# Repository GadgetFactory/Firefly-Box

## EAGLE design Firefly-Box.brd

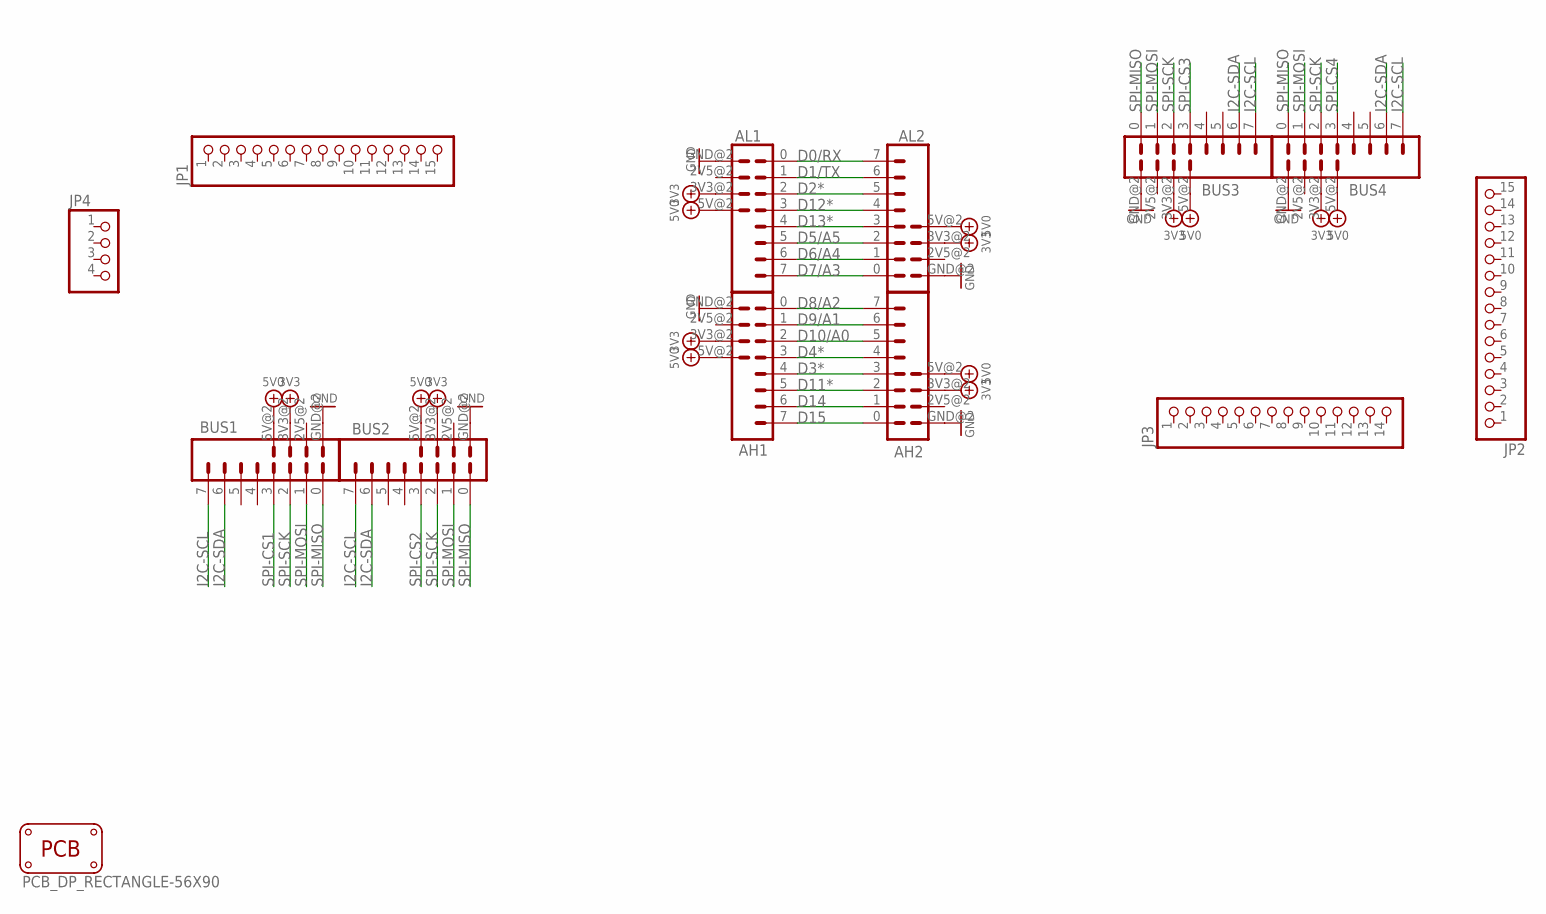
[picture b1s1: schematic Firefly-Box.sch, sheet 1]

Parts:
AH1, AH2: WING8WING8_NOHOLES; WINGSIDE_8BIT_NOHOLES
AL1, AL2: WING8WING8_NOHOLES; WINGSIDE_8BIT_NOHOLES
BUS1, BUS2, BUS3, BUS4: WING8WING8_NOHOLES; WINGSIDE_8BIT_NOHOLES
JP1, JP2: PINHD-1X15; 1X15
JP3: PINHD-1X14; 1X14
JP4: PINHD-1X4; 1X04
PCB2: PCB_DP_RECTANGLE-56X90; DP9056_V1

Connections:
3V3: AH1.3V3@2 (3V3), AH2.3V3@2 (3V3), AL1.3V3@2 (3V3), AL2.3V3@2 (3V3), BUS1.3V3@2 (3V3), BUS2.3V3@2 (3V3), BUS3.3V3@2 (3V3), BUS4.3V3@2 (3V3); also elsewhere on the board
5V0: AH1.5V@2 (5V), AH2.5V@2 (5V), AL1.5V@2 (5V), AL2.5V@2 (5V), BUS1.5V@2 (5V), BUS2.5V@2 (5V), BUS3.5V@2 (5V), BUS4.5V@2 (5V); also elsewhere on the board
D0/RX: AL1.0 (1), AL2.7 (8); also elsewhere on the board
D1/TX: AL1.1 (2), AL2.6 (7); also elsewhere on the board
D2*: AL1.2 (3), AL2.5 (6); also elsewhere on the board
D3*: AH1.4 (5), AH2.3 (4); also elsewhere on the board
D4*: AH1.3 (4), AH2.4 (5); also elsewhere on the board
D5/A5: AL1.5 (6), AL2.2 (3); also elsewhere on the board
D6/A4: AL1.6 (7), AL2.1 (2); also elsewhere on the board
D7/A3: AL1.7 (8), AL2.0 (1); also elsewhere on the board
D8/A2: AH1.0 (1), AH2.7 (8); also elsewhere on the board
D9/A1: AH1.1 (2), AH2.6 (7); also elsewhere on the board
D10/A0: AH1.2 (3), AH2.5 (6); also elsewhere on the board
D11*: AH1.5 (6), AH2.2 (3); also elsewhere on the board
D12*: AL1.3 (4), AL2.4 (5); also elsewhere on the board
D13*: AL1.4 (5), AL2.3 (4); also elsewhere on the board
D14: AH1.6 (7), AH2.1 (2); also elsewhere on the board
D15: AH1.7 (8), AH2.0 (1); also elsewhere on the board
GND: AH1.GND@2 (GND), AH2.GND@2 (GND), AL1.GND@2 (GND), AL2.GND@2 (GND), BUS1.GND@2 (GND), BUS2.GND@2 (GND), BUS3.GND@2 (GND), BUS4.GND@2 (GND); also elsewhere on the board
I2C-SCL: BUS1.7 (8), BUS2.7 (8), BUS3.7 (8), BUS4.7 (8); also elsewhere on the board
I2C-SDA: BUS1.6 (7), BUS2.6 (7), BUS3.6 (7), BUS4.6 (7); also elsewhere on the board
SPI-CS1: BUS1.3 (4); also elsewhere on the board
SPI-CS2: BUS2.3 (4); also elsewhere on the board
SPI-CS3: BUS3.3 (4); also elsewhere on the board
SPI-CS4: BUS4.3 (4); also elsewhere on the board
SPI-MISO: BUS1.0 (1), BUS2.0 (1), BUS3.0 (1), BUS4.0 (1); also elsewhere on the board
SPI-MOSI: BUS1.1 (2), BUS2.1 (2), BUS3.1 (2), BUS4.1 (2); also elsewhere on the board
SPI-SCK: BUS1.2 (3), BUS2.2 (3), BUS3.2 (3), BUS4.2 (3); also elsewhere on the board

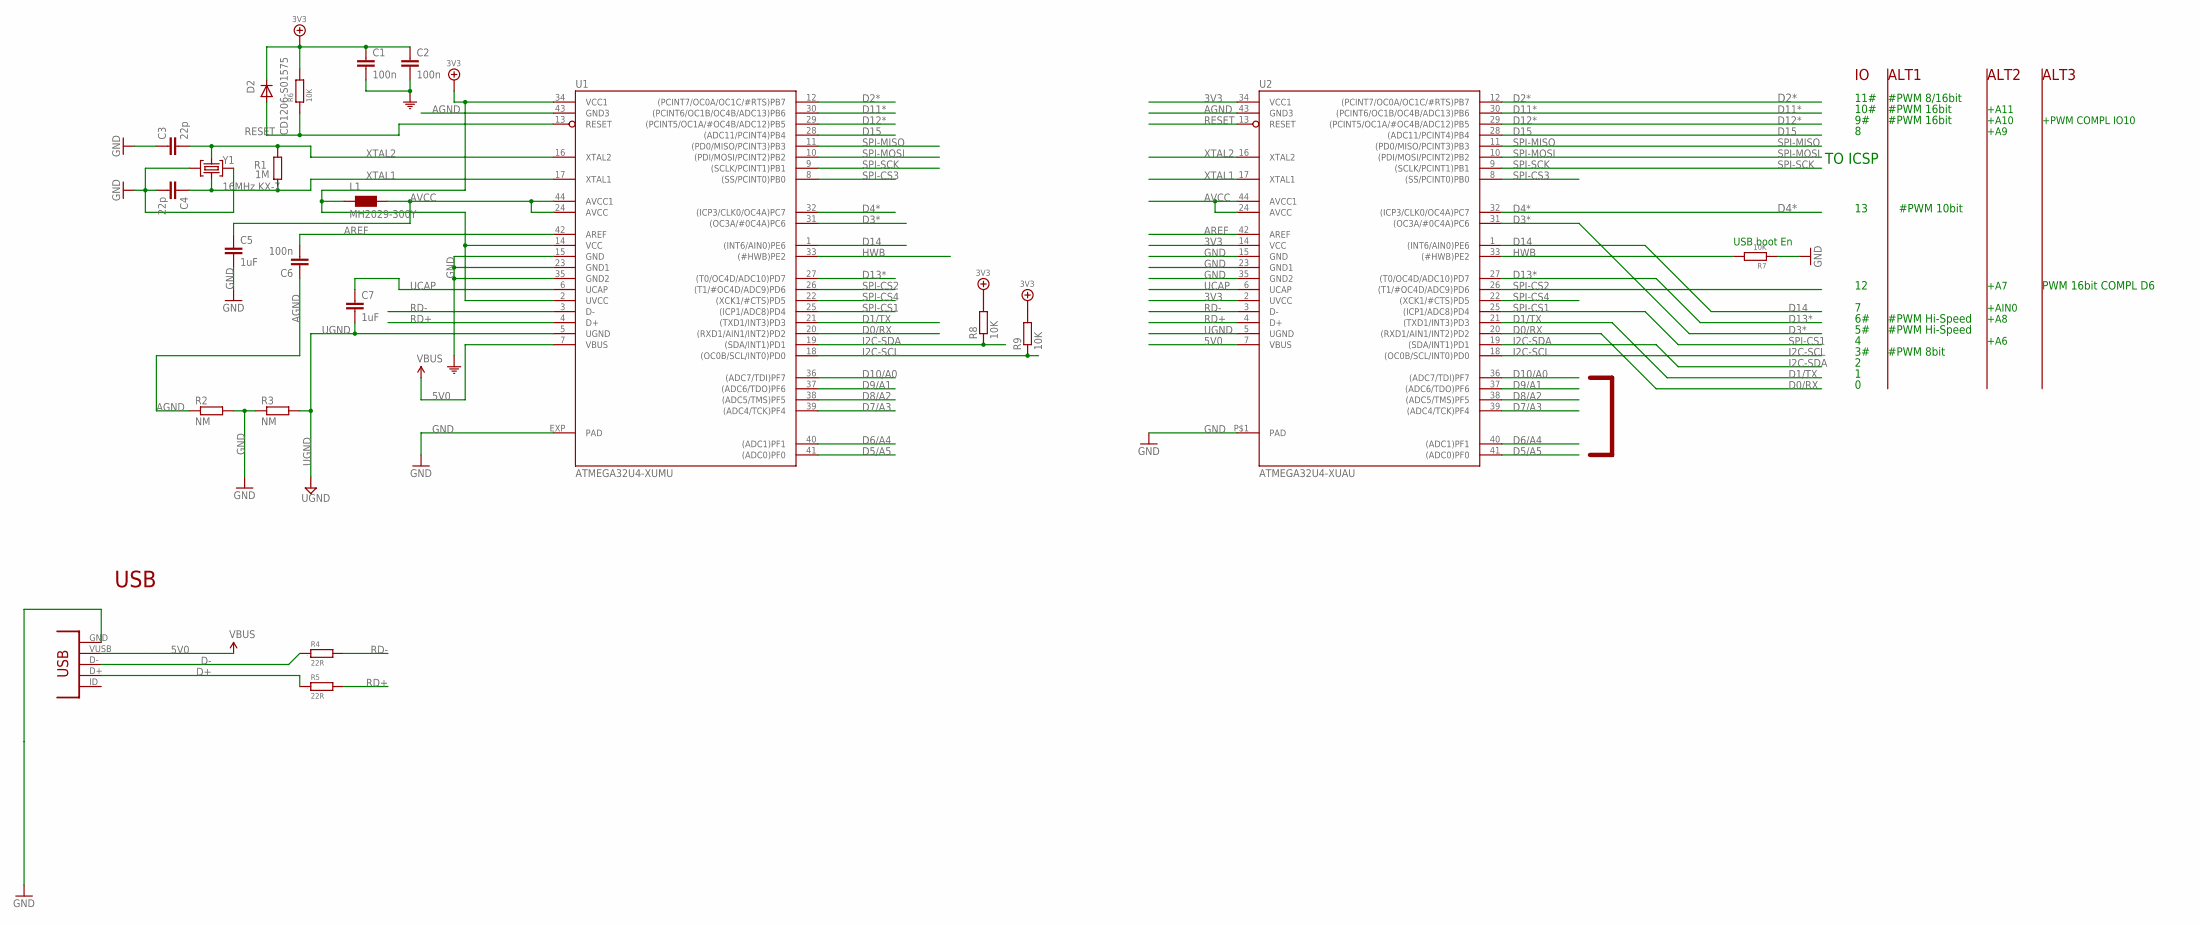
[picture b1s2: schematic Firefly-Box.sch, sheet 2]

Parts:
C1, C2, C6: 100n; C0603-ROUND
C3, C4: 22p; C0603-ROUND
C5, C7: 1uF; C0603-ROUND
CONN2: CONN_USB; CONN_USB_MINI-B
D2: CD1206-S01575; MINIMELF
L1: MH2029-300Y; 0805
R1: 1M; R0603-ROUND
R2, R3: NM; R0402
R4, R5: 22R; 0805
R6, R7: 10K; 0805
R8, R9: 10K; R0402
U1: ATMEGA32U4-XUMU; QFN44ML7X7
U2: ATMEGA32U4-XUAU; TQFP44-PAD
Y1: 16MHz KX-7; CRYSTAL-3.2-2.5

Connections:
3V3: C1.1, C2.1, D2.C, L1.1, R6.2, R8.2, R9.2, U1.2 (UVCC), U1.14 (VCC), U1.34 (VCC1), U2.2 (UVCC), U2.14 (VCC), U2.34 (VCC1); also elsewhere on the board
5V0: CONN2.VUSB, U1.7 (VBUS), U2.7 (VBUS); also elsewhere on the board
AGND: C6.1, R2.1, U1.43 (GND3), U2.43 (GND3)
AREF: C6.2, U1.42 (AREF), U2.42 (AREF)
AVCC: C5.1, L1.2, U1.24 (AVCC), U1.44 (AVCC1), U2.24 (AVCC), U2.44 (AVCC1)
D0/RX: U1.20 ((RXD1/AIN1/INT2)PD2), U2.20 ((RXD1/AIN1/INT2)PD2); also elsewhere on the board
D1/TX: U1.21 ((TXD1/INT3)PD3), U2.21 ((TXD1/INT3)PD3); also elsewhere on the board
D2*: U1.12 ((PCINT7/OC0A/OC1C/#RTS)PB7), U2.12 ((PCINT7/OC0A/OC1C/#RTS)PB7); also elsewhere on the board
D3*: U1.31 ((OC3A/#0C4A)PC6), U2.31 ((OC3A/#0C4A)PC6); also elsewhere on the board
D4*: U1.32 ((ICP3/CLK0/OC4A)PC7), U2.32 ((ICP3/CLK0/OC4A)PC7); also elsewhere on the board
D5/A5: U1.41 ((ADC0)PF0), U2.41 ((ADC0)PF0); also elsewhere on the board
D6/A4: U1.40 ((ADC1)PF1), U2.40 ((ADC1)PF1); also elsewhere on the board
D7/A3: U1.39 ((ADC4/TCK)PF4), U2.39 ((ADC4/TCK)PF4); also elsewhere on the board
D8/A2: U1.38 ((ADC5/TMS)PF5), U2.38 ((ADC5/TMS)PF5); also elsewhere on the board
D9/A1: U1.37 ((ADC6/TDO)PF6), U2.37 ((ADC6/TDO)PF6); also elsewhere on the board
D10/A0: U1.36 ((ADC7/TDI)PF7), U2.36 ((ADC7/TDI)PF7); also elsewhere on the board
D11*: U1.30 ((PCINT6/OC1B/OC4B/ADC13)PB6), U2.30 ((PCINT6/OC1B/OC4B/ADC13)PB6); also elsewhere on the board
D12*: U1.29 ((PCINT5/OC1A/#OC4B/ADC12)PB5), U2.29 ((PCINT5/OC1A/#OC4B/ADC12)PB5); also elsewhere on the board
D13*: U1.27 ((T0/OC4D/ADC10)PD7), U2.27 ((T0/OC4D/ADC10)PD7); also elsewhere on the board
D14: U1.1 ((INT6/AIN0)PE6), U2.1 ((INT6/AIN0)PE6); also elsewhere on the board
D15: U1.28 ((ADC11/PCINT4)PB4), U2.28 ((ADC11/PCINT4)PB4); also elsewhere on the board
D+: CONN2.D+, R5.1
D-: CONN2.D-, R4.1
GND: C1.2, C2.2, C3.1, C4.2, C5.2, CONN2.GND, R2.2, R3.1, R7.1, U1.15 (GND), U1.23 (GND1), U1.35 (GND2), U1.EXP (PAD), U2.15 (GND), U2.23 (GND1), U2.35 (GND2), U2.P$1 (PAD), Y1.2 (GND), Y1.4 (GND); also elsewhere on the board
HWB: R7.2, U1.33 ((#HWB)PE2), U2.33 ((#HWB)PE2)
I2C-SCL: R9.1, U1.18 ((OC0B/SCL/INT0)PD0), U2.18 ((OC0B/SCL/INT0)PD0); also elsewhere on the board
I2C-SDA: R8.1, U1.19 ((SDA/INT1)PD1), U2.19 ((SDA/INT1)PD1); also elsewhere on the board
RD+: R5.2, U1.4 (D+), U2.4 (D+)
RD-: R4.2, U1.3 (D-), U2.3 (D-)
RESET: D2.A, R6.1, U1.13 (RESET), U2.13 (RESET)
SPI-CS1: U1.25 ((ICP1/ADC8)PD4), U2.25 ((ICP1/ADC8)PD4); also elsewhere on the board
SPI-CS2: U1.26 ((T1/#OC4D/ADC9)PD6), U2.26 ((T1/#OC4D/ADC9)PD6); also elsewhere on the board
SPI-CS3: U1.8 ((SS/PCINT0)PB0), U2.8 ((SS/PCINT0)PB0); also elsewhere on the board
SPI-CS4: U1.22 ((XCK1/#CTS)PD5), U2.22 ((XCK1/#CTS)PD5); also elsewhere on the board
SPI-MISO: U1.11 ((PD0/MISO/PCINT3)PB3), U2.11 ((PD0/MISO/PCINT3)PB3); also elsewhere on the board
SPI-MOSI: U1.10 ((PDI/MOSI/PCINT2)PB2), U2.10 ((PDI/MOSI/PCINT2)PB2); also elsewhere on the board
SPI-SCK: U1.9 ((SCLK/PCINT1)PB1), U2.9 ((SCLK/PCINT1)PB1); also elsewhere on the board
UCAP: C7.1, U1.6 (UCAP), U2.6 (UCAP)
UGND: C7.2, R3.2, U1.5 (UGND), U2.5 (UGND)
XTAL1: C4.1, R1.1, U1.17 (XTAL1), U2.17 (XTAL1), Y1.1 (C1)
XTAL2: C3.2, R1.2, U1.16 (XTAL2), U2.16 (XTAL2), Y1.3 (C2)

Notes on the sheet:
USB boot En
USB
TO ICSP
10#
11#
#PWM 8bit
#PWM Hi-Speed
#PWM 8/16bit
#PWM 16bit
PWM 16bit COMPL D6
#PWM 10bit
+A6
+A7
+A11
+A10
+A8
+A9
+PWM COMPL IO10
+AIN0
ALT1
ALT2
ALT3

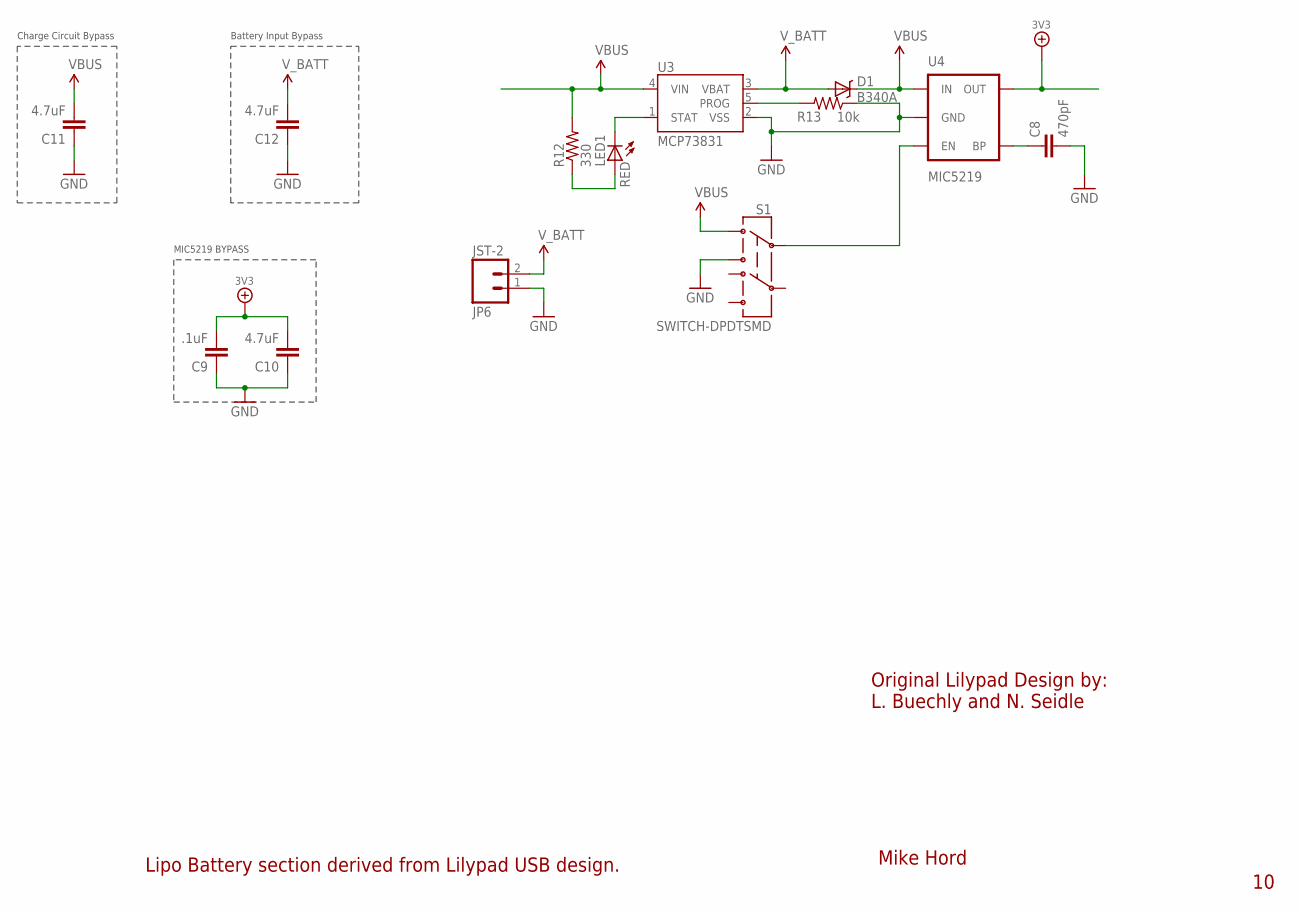
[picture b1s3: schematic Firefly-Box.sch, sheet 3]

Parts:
C8: 470pF; 0603-CAP
C9: .1uF; 0603-CAP
C10: 4.7uF; 0603-CAP
C11, C12: 4.7uF; 1206
D1: B340A; SMA-DIODE
JP6: JST-2; JST-2-SMD
LED1: RED; LED-0603
R12: 330; 0603-RES
R13: 10k; 0603-RES
S1: SWITCH-DPDTSMD; AYZ0202
U3: MCP73831; SOT23-5
U4: MIC5219; SOT23-5

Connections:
3V3: C9.2, C10.2, U4.5 (OUT); also elsewhere on the board
5V0: C11.2, D1.C, R12.2, S1.1, U3.4 (VIN), U4.1 (IN); also elsewhere on the board
GND: C8.2, C9.1, C10.1, C11.1, C12.1, JP6.1 (2), R13.1, S1.3, U3.2 (VSS), U4.2 (GND); also elsewhere on the board
unnamed: S1.2, U4.3 (EN)
unnamed: LED1.A, R12.1
unnamed: LED1.C, U3.1 (STAT)
unnamed: R13.2, U3.5 (PROG)
unnamed: C8.1, U4.4 (BP)
V_BATT: C12.2, D1.A, JP6.2 (1), U3.3 (VBAT)

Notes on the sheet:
MIC5219 BYPASS
Mike Hord
Original Lilypad Design by:
L. Buechly and N. Seidle
Charge Circuit Bypass
Battery Input Bypass
Lipo Battery section derived from Lilypad USB design.

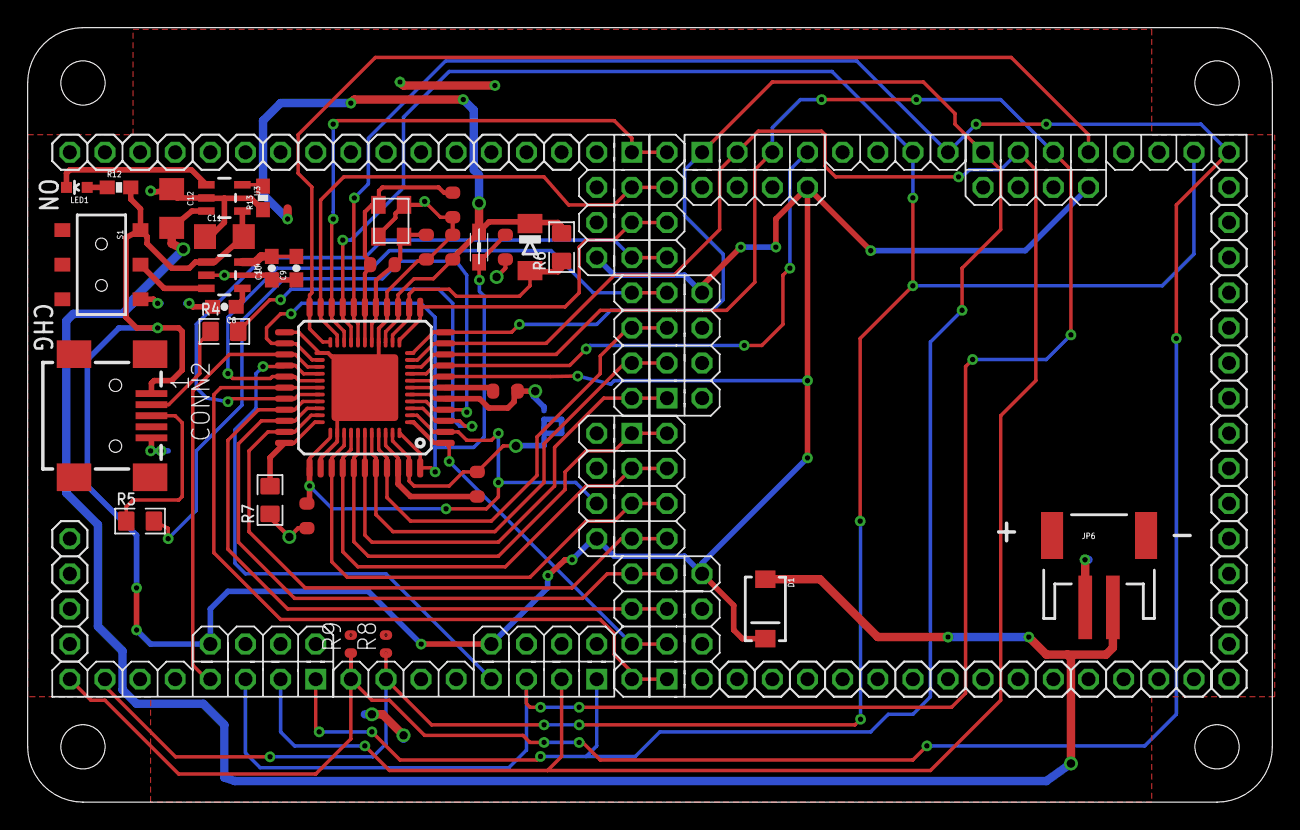
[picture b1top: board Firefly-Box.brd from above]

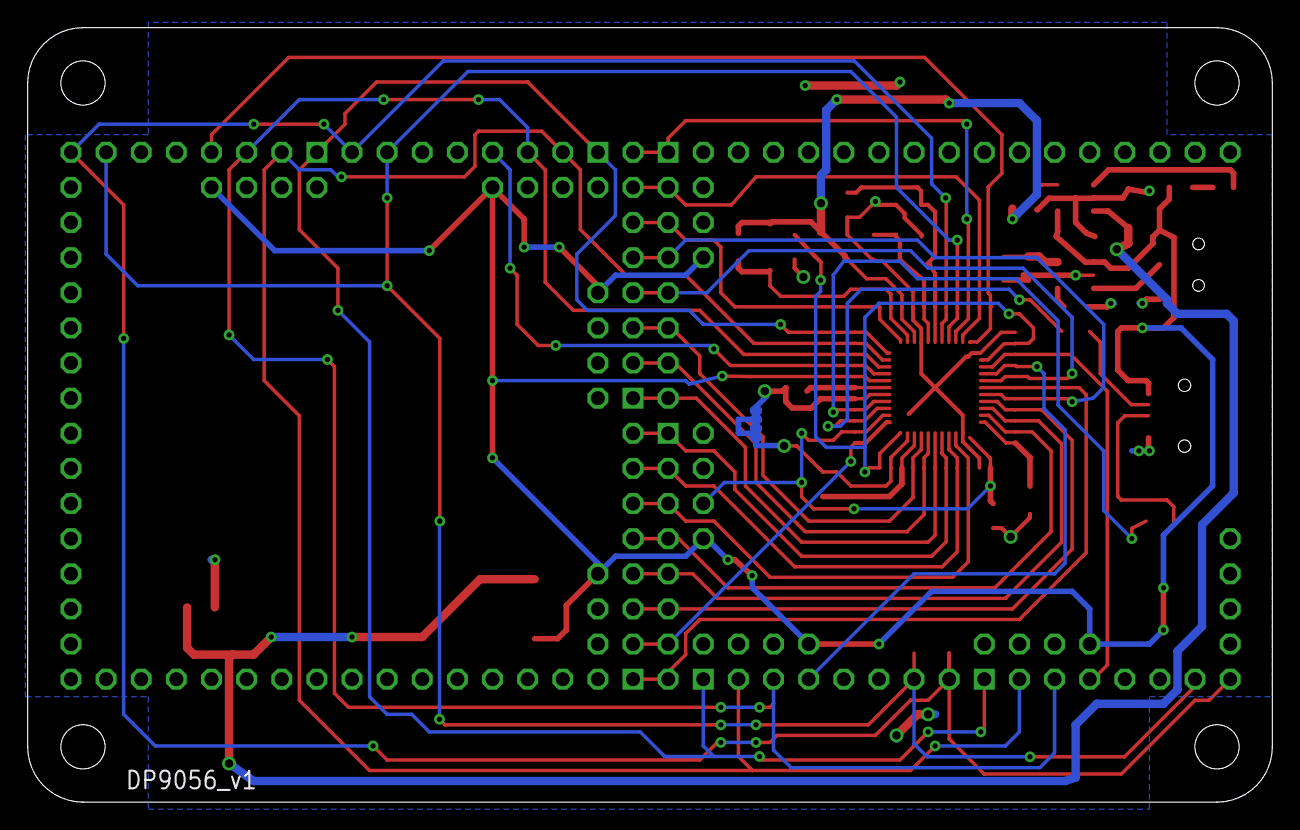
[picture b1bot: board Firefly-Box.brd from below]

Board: 2 copper layers, 90.0 x 56.0 mm, 48 parts (2 on the bottom side), 47 nets.

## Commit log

2015-05-26 :boom::camel: Added .gitattributes & .gitignore files
2015-05-26 Locations placed and test routing.
2015-05-26 Fixed pin names
2015-05-26 Add Box headers
2015-05-26 Add power to wings
2015-05-28 Added Power and LiPo section.
2015-05-28 Lots of routing done.
2015-05-29 Fully Routed

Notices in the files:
parts and their libraries:
SparkFun-PowerIC: Licensing: CC v3.0 Share-Alike You are welcome to use this library for commercial purposes.
SparkFun-Aesthetics: Released under the Creative Commons
SparkFun-Aesthetics: http://creativecommons.org/licenses/by-sa/3.0
